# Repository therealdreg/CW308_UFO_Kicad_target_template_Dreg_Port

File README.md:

# CW308_UFO_target_template_Dreg_Port

chipwhisper UFO CW308 TARGET template for KiCad with Dreg port (and easyeda file to import)

-----

# PCB

- ENIG
- PCB Size: 52.3mm x 64.6mm
- 2 layers
- male pins 

UFO BOARD SOCKET FEMALE:

-----

# MALE PINS

- 800-10-020-10-001101
- Preci-dip
- https://www.mouser.es/ProductDetail/437-8001002010001101

-----

# FEMALE PINS
- 801-87-020-10-001101
- Preci-dip
- https://www.mouser.es/ProductDetail/437-8018702010001101

------

# kicad project 

[CW308T_AVR_Kicad_Dreg_Port.zip](CW308T_AVR_Kicad_Dreg_Port.zip)

------

# easyeda pro file to import

[ProPrj_CW308T_AVR_Kicad_Dreg_Port_2026-06-29.epro2](ProPrj_CW308T_AVR_Kicad_Dreg_Port_2026-06-29.epro2)

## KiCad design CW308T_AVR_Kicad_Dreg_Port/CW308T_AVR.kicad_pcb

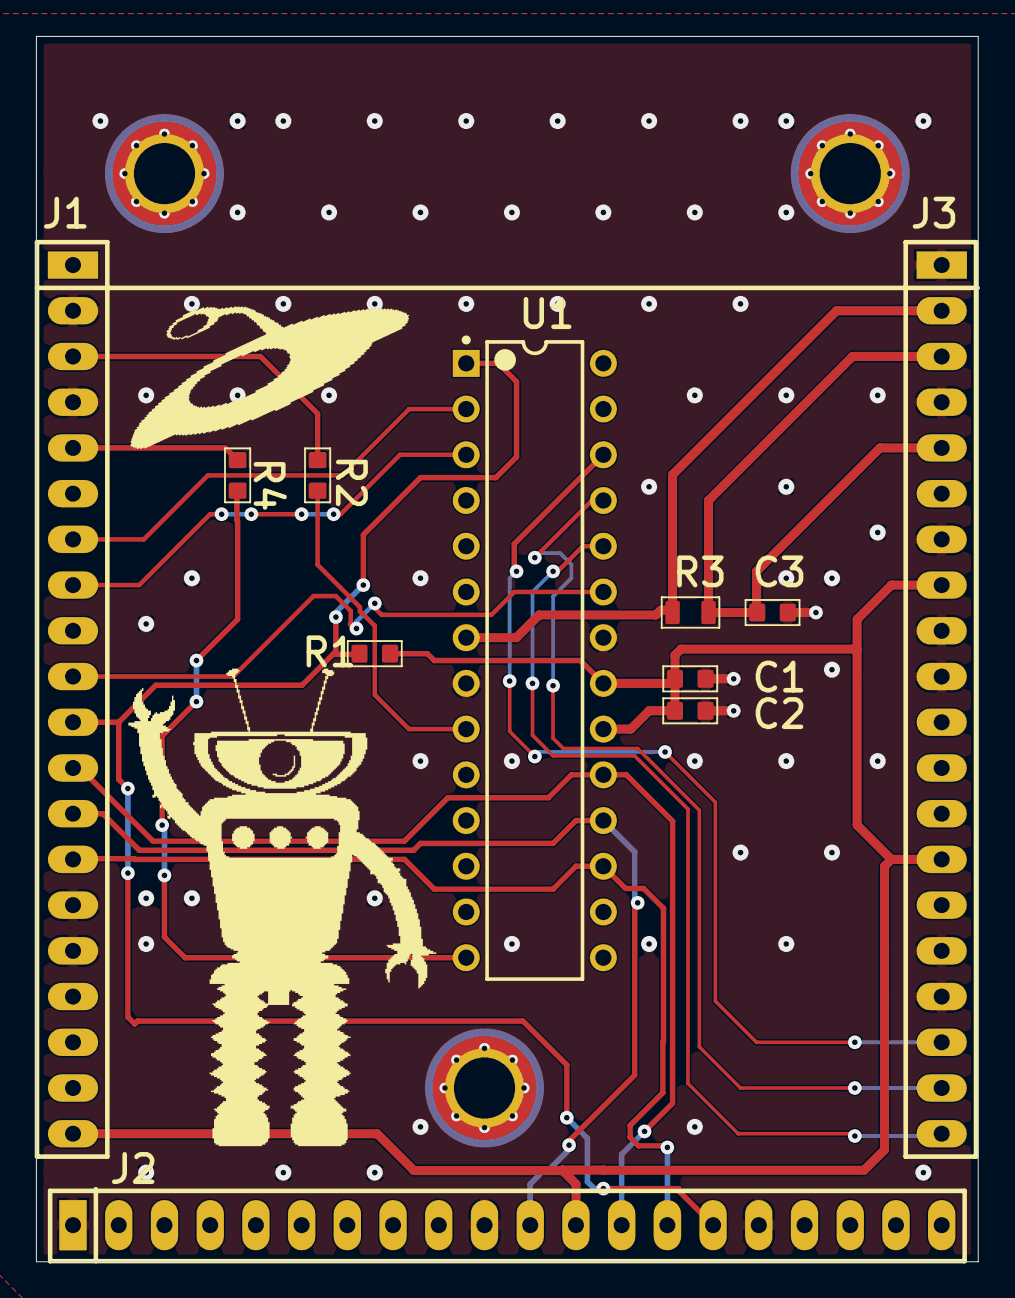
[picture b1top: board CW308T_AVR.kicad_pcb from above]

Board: 2 copper layers, 52.3 x 68.1 mm, 14 parts (0 on the bottom side), 18 nets.

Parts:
C1, C2, C3: approved sub OK; CAPC1608X90N
J1, J2, J3: 20-Pin Header; 801-87-020-10-001101
MH3, MH4, MH5: Mounting-Hole-RND-Altium
R1, R2, R4: Thick Film; RESC1608X55N
R3: Thick Film; RESC2012X70N
U1: ATmega328P-PU; 28P3

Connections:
CLKIN: J1.3, R2.2
CLKOUT: J1.5, R4.2
FILTIN: C1.1, C2.1, J1.20, J2.12, J3.8, J3.14, R1.1, U1.20, U1.21
FILT_LP: C3.1, J3.3, J3.5, R3.2
GND: C1.2, C2.2, C3.2, J1.2, J1.4, J1.6, J1.15, J1.16, J2.1, J2.10, J2.16, J3.1, J3.4, J3.7, J3.9, J3.10, J3.16, J3.17, U1.8, U1.22
GPIO1/TX: J1.7, U1.2
GPIO2/RX: J1.8, U1.3
GPIO4/TRIG: J1.10, U1.23
LED1: J3.18, U1.26
LED2: J3.19, U1.25
LED3: J3.20, U1.24
MISO: J1.13, J2.11, U1.18
MOSI: J1.14, J2.14, U1.17
NRST: J1.11, J2.15, R1.2, U1.1
NetR2_1: R2.1, U1.9
NetR4_1: R4.1, U1.14
SCK: J1.12, J2.13, U1.19
SHUNTL: J3.2, R3.1, U1.7

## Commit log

2026-06-29 first version
2026-06-29 Add funding sources for GitHub and Patreon
    Updated funding sources with specific usernames and links.

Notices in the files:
parts and their libraries:
PRJLICENSE: GPL
